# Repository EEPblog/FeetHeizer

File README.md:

# FeetHeizer
A project, that keeps your feet warm during winter!
This project is sponsored by PCBgogo: www.pcbgogo.com?code=t

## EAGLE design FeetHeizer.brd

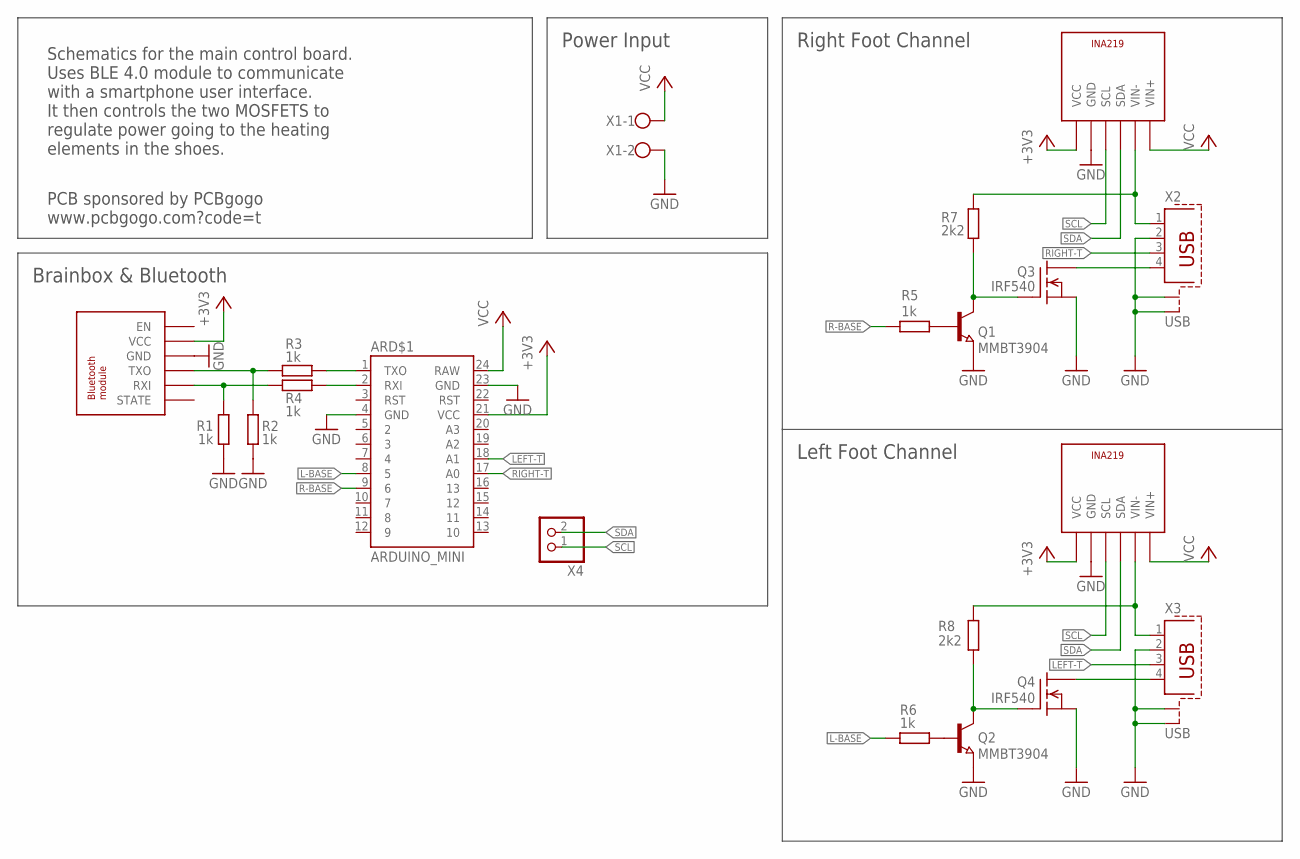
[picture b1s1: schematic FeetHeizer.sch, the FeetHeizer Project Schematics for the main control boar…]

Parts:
ARD$1: ARDUINO_MINI
MODULE1: BT; HC10
MODULE2, MODULE3: INA
Q1, Q2: MMBT3904; SOT23
Q3, Q4: IRF540; TO220
R1, R2, R3, R4, R5, R6: 1k; R0805
R7, R8: 2k2; R0805
X1: W237-102
X2, X3: USB; PN87520-S
X4: PINHD-1X2_2.54; 1X02

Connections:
+3V3: ARD$1.21 (VCC), MODULE1.VCC, MODULE2.VCC, MODULE3.VCC
GND: ARD$1.4 (GND), ARD$1.23 (GND), MODULE1.GND, MODULE2.GND, MODULE3.GND, Q1.2 (E), Q2.2 (E), Q3.3 (S), Q4.3 (S), R1.2, R2.2, X1.2, X2.2, X2.S1, X2.S2, X3.2, X3.S1, X3.S2
L-BASE: ARD$1.8 (5), R6.2
LEFT-T: ARD$1.18 (A1), X3.3
unnamed: Q1.3 (C), Q3.1 (G), R7.1
unnamed: Q3.2 (D), X2.4
unnamed: Q1.1 (B), R5.1
unnamed: Q2.3 (C), Q4.1 (G), R8.1
unnamed: Q2.1 (B), R6.1
unnamed: Q4.2 (D), X3.4
unnamed: MODULE1.RXD (RXI), R1.1, R4.2
unnamed: ARD$1.1 (TXO), R3.1
unnamed: MODULE1.TXD (TXO), R2.1, R3.2
unnamed: ARD$1.2 (RXI), R4.1
unnamed: MODULE2.VIN-, R7.2, X2.1
unnamed: MODULE3.VIN-, R8.2, X3.1
R-BASE: ARD$1.9 (6), R5.2
RIGHT-T: ARD$1.17 (A0), X2.3
SCL: MODULE2.SCL, MODULE3.SCL, X4.1
SDA: MODULE2.SDA, MODULE3.SDA, X4.2
VCC: ARD$1.24 (RAW), MODULE2.VIN+, MODULE3.VIN+, X1.1

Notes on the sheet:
Schematics for the main control board. Uses BLE 4.0 module to communicate with a smartphone user interface. It then controls the two MOSFETS to regulate power going to the heating elements in the shoes.
Right Foot Channel
Left Foot Channel
Brainbox & Bluetooth
Power Input
PCB sponsored by PCBgogo www.pcbgogo.com?code=t

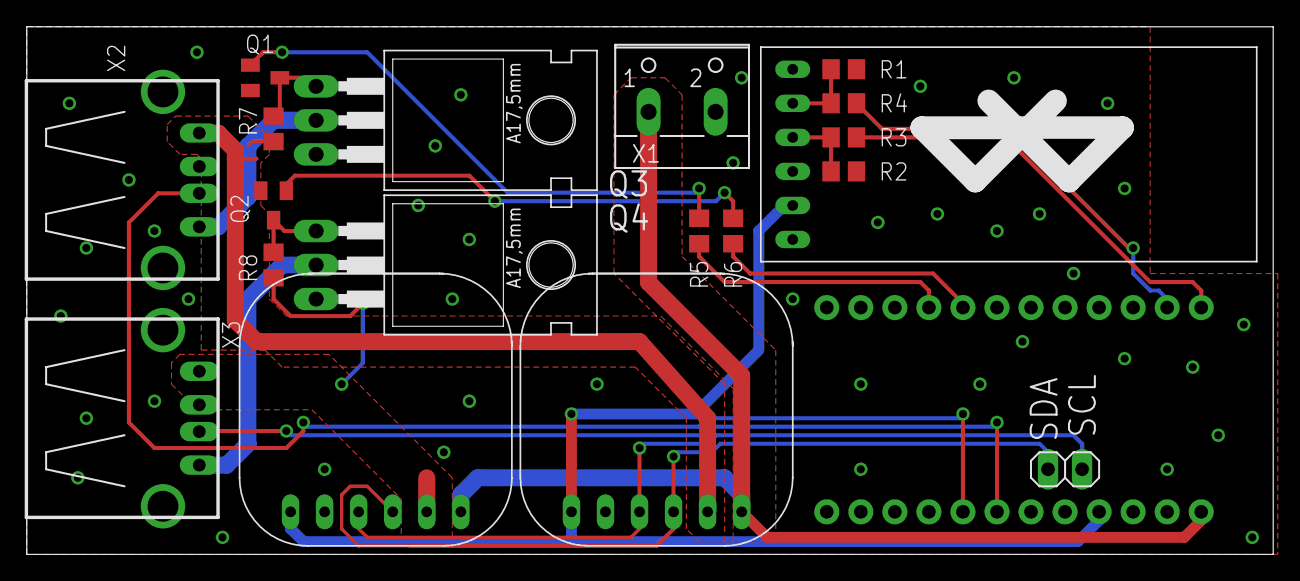
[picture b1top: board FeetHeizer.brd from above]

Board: 2 copper layers, 93.0 x 39.4 mm, 20 parts (0 on the bottom side), 21 nets.

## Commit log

2018-10-16 Rename FeetHEizer - Copy.brd to FeetHeizer.brd
2018-10-16 Rename FeetHEizer - Copy.sch to FeetHeizer.sch

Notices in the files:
FeetHeizer.brd:
(c) 2018 Angelo Pescarini
parts and their libraries:
SparkFun-Boards: Licensing: Creative Commons ShareAlike 4.0 International - https://creativecommons.org/licenses/by-sa/4.0
